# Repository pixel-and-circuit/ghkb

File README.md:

GHKB

<picture>
  <source media="(prefers-color-scheme: dark)" srcset="docs/images/case-preview-dark.png">
  
</picture>

GHKB is an open-source split mechanical keyboard project focused on custom hardware, modern firmware, and long-term experimentation.

The goal of this project is to build a fully custom wireless split keyboard from the ground up, including both the hardware and firmware stack. Rather than assembling an existing design, GHKB documents the complete engineering process—from PCB and enclosure design to firmware development.

Goals

Phase 1: Build a Reliable Daily Driver

Develop a fully functional wireless split keyboard featuring:

* Custom PCB designed with KiCad (single reversible design shared by both halves)
* Custom 3D-printed enclosure
* MX-compatible mechanical switches on hotswap sockets
* Battery-powered operation
* Bluetooth Low Energy (BLE)
* ZMK firmware
* Comfortable ergonomic layout

Controller strategy: the first prototype targets an off-the-shelf nRF52840
controller module (e.g. Nice!Nano) socketed onto the PCB. Designing a fully
custom controller—placing the nRF52840 QFN/BGA package directly on the board—is
a later, optional goal once the socketed design is validated.

Hardware design decisions:

* Layout: 42 keys — a 3x6 column-staggered matrix plus a 3-key thumb cluster
  per half (Corne-style), with an optional EC11 rotary encoder position.
* PCB: one reversible PCB serves both halves (components mount on the front
  for one half and on the back for the other), halving design and
  manufacturing effort.
* Switches: MX hotswap sockets (Kailh), so the prototype can be reworked
  without desoldering.
* Display: none. A display only shows status (battery, layer, BLE profile)
  and is not needed for keyboard operation; omitting it saves cost, battery,
  and three GPIOs kept as spares.
* RGB: deferred past Phase 1. Per-key RGB is battery-hostile on a wireless
  board; at most, unpopulated footprints are reserved.
* Layout generation: switch placement and the board outline are generated
  with ergogen and imported into KiCad, so layout iterations stay
  reproducible.

Phase 2: Develop a TinyGo Firmware

Create a native TinyGo firmware targeting the same hardware platform. The
long-term objective is not simply to recreate existing keyboard firmware, but to
explore whether a modern Go-based embedded ecosystem can become a practical
alternative for custom keyboard development.

Because the wireless BLE stack is by far the highest-risk part of this effort,
Phase 2 is split into two independent milestones:

Phase 2a: USB-wired TinyGo firmware (high feasibility)

Bring up a wired, single-board or wired-split TinyGo build using USB HID, which
is well supported in the TinyGo ecosystem and has existing precedent. This
establishes the matrix scanning, keymap, and feature layer in Go without
depending on wireless.

Phase 2b: BLE-wireless TinyGo firmware (research / uncertain)

Extend the firmware to full wireless operation. This is genuinely exploratory
and may not be achievable: TinyGo's BLE support (`tinygo.org/x/bluetooth`) has
historically centered on the central/scanner role and relies on Nordic's
SoftDevice, whereas a keyboard needs a BLE peripheral with HID-over-GATT,
pairing/bonding, and a wireless split link. ZMK gets these for free from
Zephyr's mature BLE stack; in TinyGo much of it would have to be built from
scratch. Treat Phase 2b as an open question, not a scheduled deliverable.

Planned Features

* Wireless split architecture
* Bluetooth Low Energy (BLE)
* Multi-device pairing
* Battery management
* USB-C charging
* Layer support
* Mod-Tap / Hold-Tap
* Combo keys
* Rotary encoder support
* Optional RGB lighting (post-Phase 1)
* Firmware updates via bootloader

Repository Structure

Note: this is the planned/target layout for the completed project. The
repository currently contains only this README while the project is in the
planning and hardware design phase; directories below are created as work
progresses.

```
.
├── README.md
├── HARDWARE.md
├── LICENSE
├── .gitignore
├── config/
│   ├── west.yml
│   ├── ghkb.keymap
│   └── boards/shields/ghkb/
├── build.yaml
├── firmware/
│   └── tinygo/
├── pcb/
│   ├── ergogen/
│   │   ├── config.yaml
│   │   └── footprints/
│   ├── keyboard.kicad_pro
│   ├── keyboard.kicad_sch
│   ├── keyboard.kicad_pcb
│   └── libraries/
├── case/
│   ├── source/
│   │   ├── params.py
│   │   ├── layout.py
│   │   ├── ghkb_case.py
│   │   ├── render_preview.py
│   │   ├── left.FCStd
│   │   └── right.FCStd
│   ├── exports/
│   │   ├── left.step / right.step
│   │   └── {left,right}_{top,bottom}.stl
│   └── reference/
│       └── keyboard_pcba.step
├── docs/
│   ├── assembly.md
│   ├── wiring.md
│   └── images/
│       └── case-preview{,-dark}.png
└── bom/
    └── bom.csv
```

Directory Overview

Directory	Description
HARDWARE.md	Sourcing guide: full parts table with purchase links, PCB fab options, and assembly cautions.
config	Production ZMK firmware config (west manifest, keymap, custom ghkb shield). Lives at the repo root because ZMK's reusable CI workflow expects config_path/build_matrix_path relative to the west topdir, which must be the repo root - not a nested subdirectory.
firmware/tinygo	Experimental TinyGo firmware implementation.
pcb	KiCad project files, schematics, PCB layout, and custom libraries.
pcb/ergogen	Ergogen layout source (YAML) and reversible footprint library.
case/source	Parametric enclosure build scripts (params/layout/ghkb_case.py) and the generated FreeCAD documents. The switch plate is integrated into the top shell, so there is no separate plate design. Rebuild everything with `freecadcmd case/source/ghkb_case.py`; the build asserts its geometry against the routed PCB and aborts on drift. `render_preview.py` regenerates the README preview images from the built FCStd documents (needs the FreeCAD GUI).
case/exports	Exported manufacturing files (per-half STEP, print-ready top/bottom STLs).
case/reference	kicad-cli STEP export of the routed PCB, used for interference checks.
docs	Assembly guide, wiring documentation, and project images.
bom	Bill of Materials used to build the keyboard.

Roadmap

* Finalize the keyboard layout (42-key, 3x6+3 per half)
* Design the PCB (single reversible board, ergogen + KiCad)
* Design the enclosure (integrated-plate top shell + screwed lid, parametric FreeCAD build; v1 done, pending print validation)
* Build the first prototype
* Bring up ZMK firmware
* Validate the hardware
* Use as a daily driver
* Develop USB-wired TinyGo firmware (Phase 2a)
* Investigate BLE-wireless TinyGo firmware (Phase 2b, research)
* Document the complete development process

Status

This project is currently in the planning and hardware design phase.

Contributing

Contributions are welcome.

Whether you are interested in mechanical keyboards, embedded systems, TinyGo, ZMK, PCB design, or 3D modeling, feel free to open an issue or submit a pull request.

License

This project is dual-licensed to ensure that anyone who uses, modifies, or sells
GHKB — commercially or otherwise — must release their own source under the same
copyleft terms.

- **Software / firmware / source code** (everything in `config/`, `zmk/`,
  `modules/`, `firmware/`, build scripts, documentation sources, etc.) is
  licensed under the **GNU General Public License v3.0 (GPL-3.0)** — a strong
  copyleft license. You may sell copies, but any distributed modified version
  must be released as source under GPL-3.0. See the `LICENSE` file.

- **Hardware designs** (`pcb/`, `case/`, including KiCad projects, schematics,
  PCB layouts, footprints, and 3D-printed enclosure source) are licensed under
  the **CERN Open Hardware Licence v2 – Strongly Reciprocal (CERN-OHL-S)**.
  Any product or design derived from these must have its corresponding design
  source made available under the same licence. See the `LICENSE-HARDWARE` file.

In short: **commercial sale is allowed, but reciprocity is mandatory** — if you
convey GHKB (or a derivative) to others, your modified software and hardware
source must stay open under these licenses.

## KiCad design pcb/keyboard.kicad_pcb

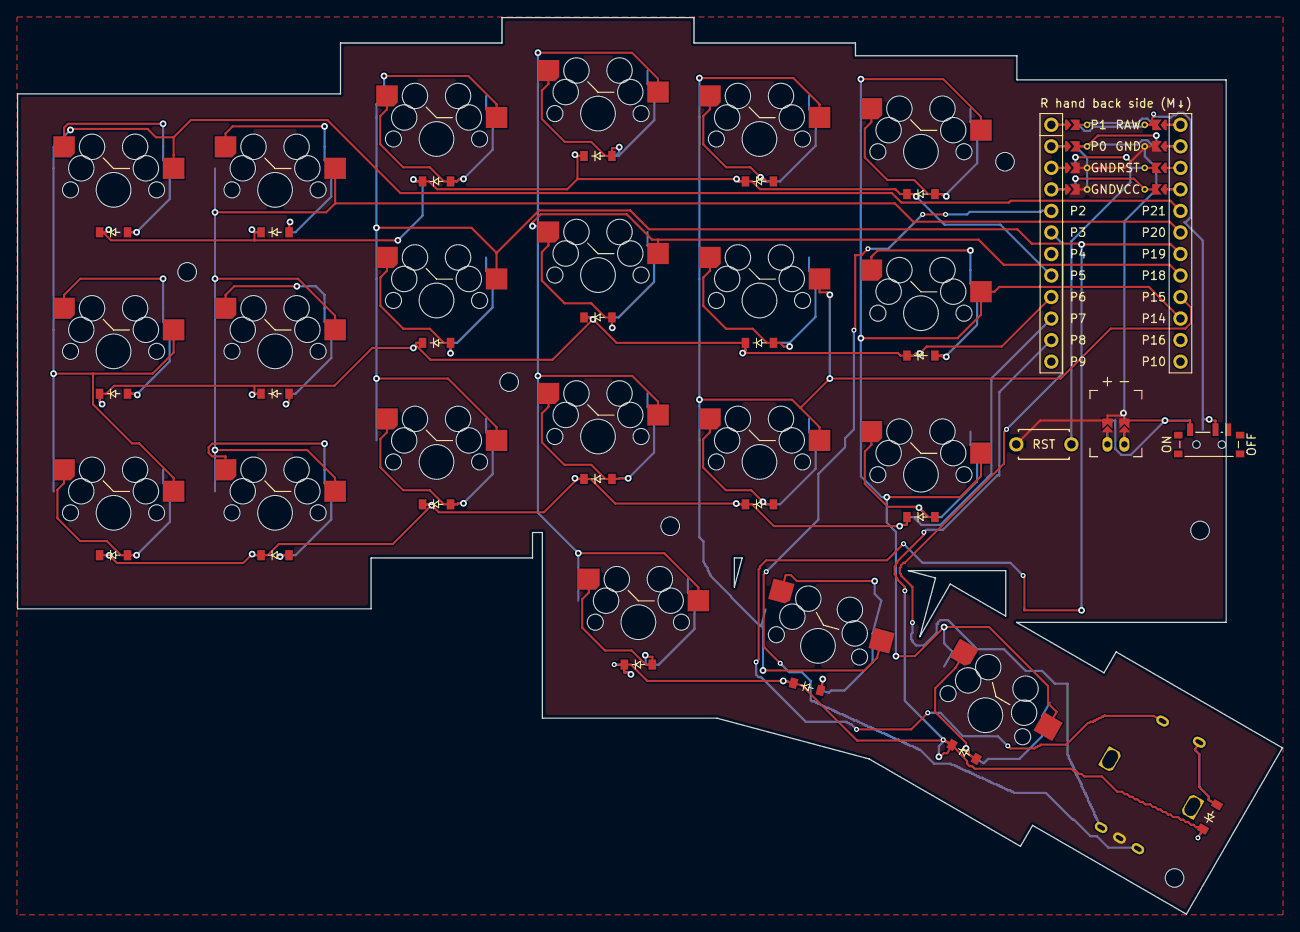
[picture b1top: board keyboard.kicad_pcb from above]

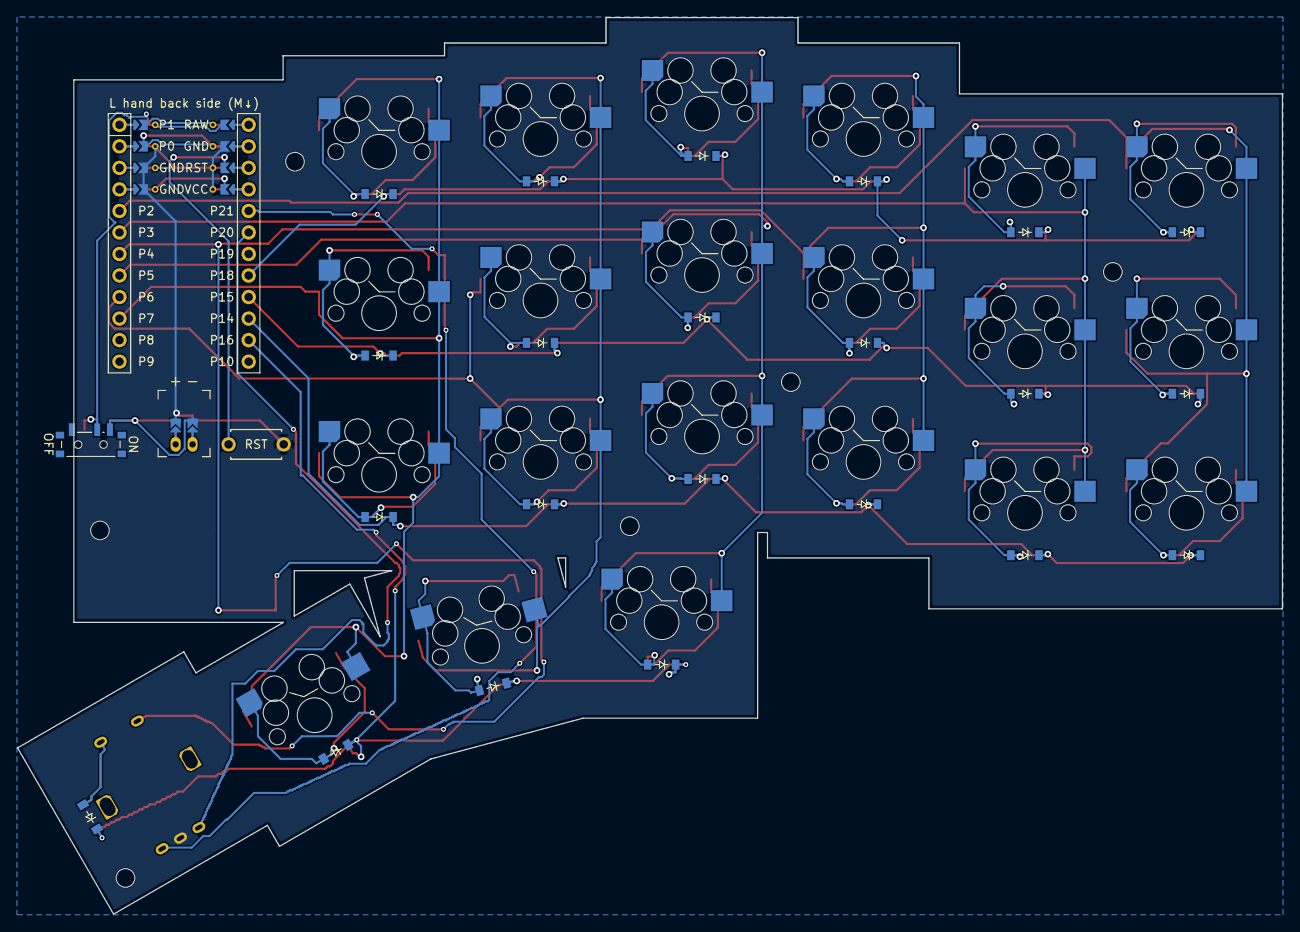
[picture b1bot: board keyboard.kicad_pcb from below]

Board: 2 copper layers, 149.2 x 105.8 mm, 54 parts (21 on the bottom side), 40 nets.

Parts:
D1, D2, D3, D4, D5, D6, D7, D8, D9, D10, D11, D12, D13, D14, D15, D16, D17, D18, D19, D20, D21, D22: diode_tht_sod123
JST1: battery_connector_jst_ph_2
MCU1: mcu_nice_nano
MH1, MH2, MH3, MH4, MH5, MH6: MountingHole_2.2mm
PWR1: power_switch_smd_side
RE1: rotary_encoder_ec11_ec12
RST1: reset_switch_tht_top
S1, S2, S3, S4, S5, S6, S7, S8, S9, S10, S11, S12, S13, S14, S15, S16, S17, S18, S19, S20, S21: switch_mx

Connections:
BAT_P: JST1.1, PWR1.1, PWR1.3
GND: JST1.2, MCU1.102, MCU1.121, MCU1.122, RE1.B, RST1.2
JST1_1: JST1.11, JST1.21, JST1.31
JST1_2: JST1.12, JST1.22, JST1.32
P2: MCU1.20, RE1.A
P3: MCU1.19, RE1.C
P5: D3.1, D6.1, D9.1, D12.1, D15.1, D18.1, MCU1.17
P6: D2.1, D5.1, D8.1, D11.1, D14.1, D17.1, MCU1.16
P7: D1.1, D4.1, D7.1, D10.1, D13.1, D16.1, MCU1.15
P8: D19.1, D20.1, D21.1, D22.1, MCU1.14
P14: MCU1.10, S16.1, S17.1, S18.1, S21.1
P15: MCU1.9, S13.1, S14.1, S15.1, S20.1
P18: MCU1.8, S10.1, S11.1, S12.1, S19.1
P19: MCU1.7, RE1.S1, S7.1, S8.1, S9.1
P20: MCU1.6, S4.1, S5.1, S6.1
P21: MCU1.5, S1.1, S2.1, S3.1
RAW: MCU1.101, PWR1.2
RST: MCU1.103, RST1.1
enc: D22.2, RE1.S2
far_thumb: D21.2, S21.2
home_thumb: D20.2, S20.2
index_bottom: D13.2, S13.2
index_home: D14.2, S14.2
index_top: D15.2, S15.2
inner_bottom: D16.2, S16.2
inner_home: D17.2, S17.2
inner_top: D18.2, S18.2
middle_bottom: D10.2, S10.2
middle_home: D11.2, S11.2
middle_top: D12.2, S12.2
near_thumb: D19.2, S19.2
outer_bottom: D1.2, S1.2
outer_home: D2.2, S2.2
outer_top: D3.2, S3.2
pinky_bottom: D4.2, S4.2
pinky_home: D5.2, S5.2
pinky_top: D6.2, S6.2
ring_bottom: D7.2, S7.2
ring_home: D8.2, S8.2
ring_top: D9.2, S9.2
